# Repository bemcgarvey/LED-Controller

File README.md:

# LED Controller
 RC LED Controller

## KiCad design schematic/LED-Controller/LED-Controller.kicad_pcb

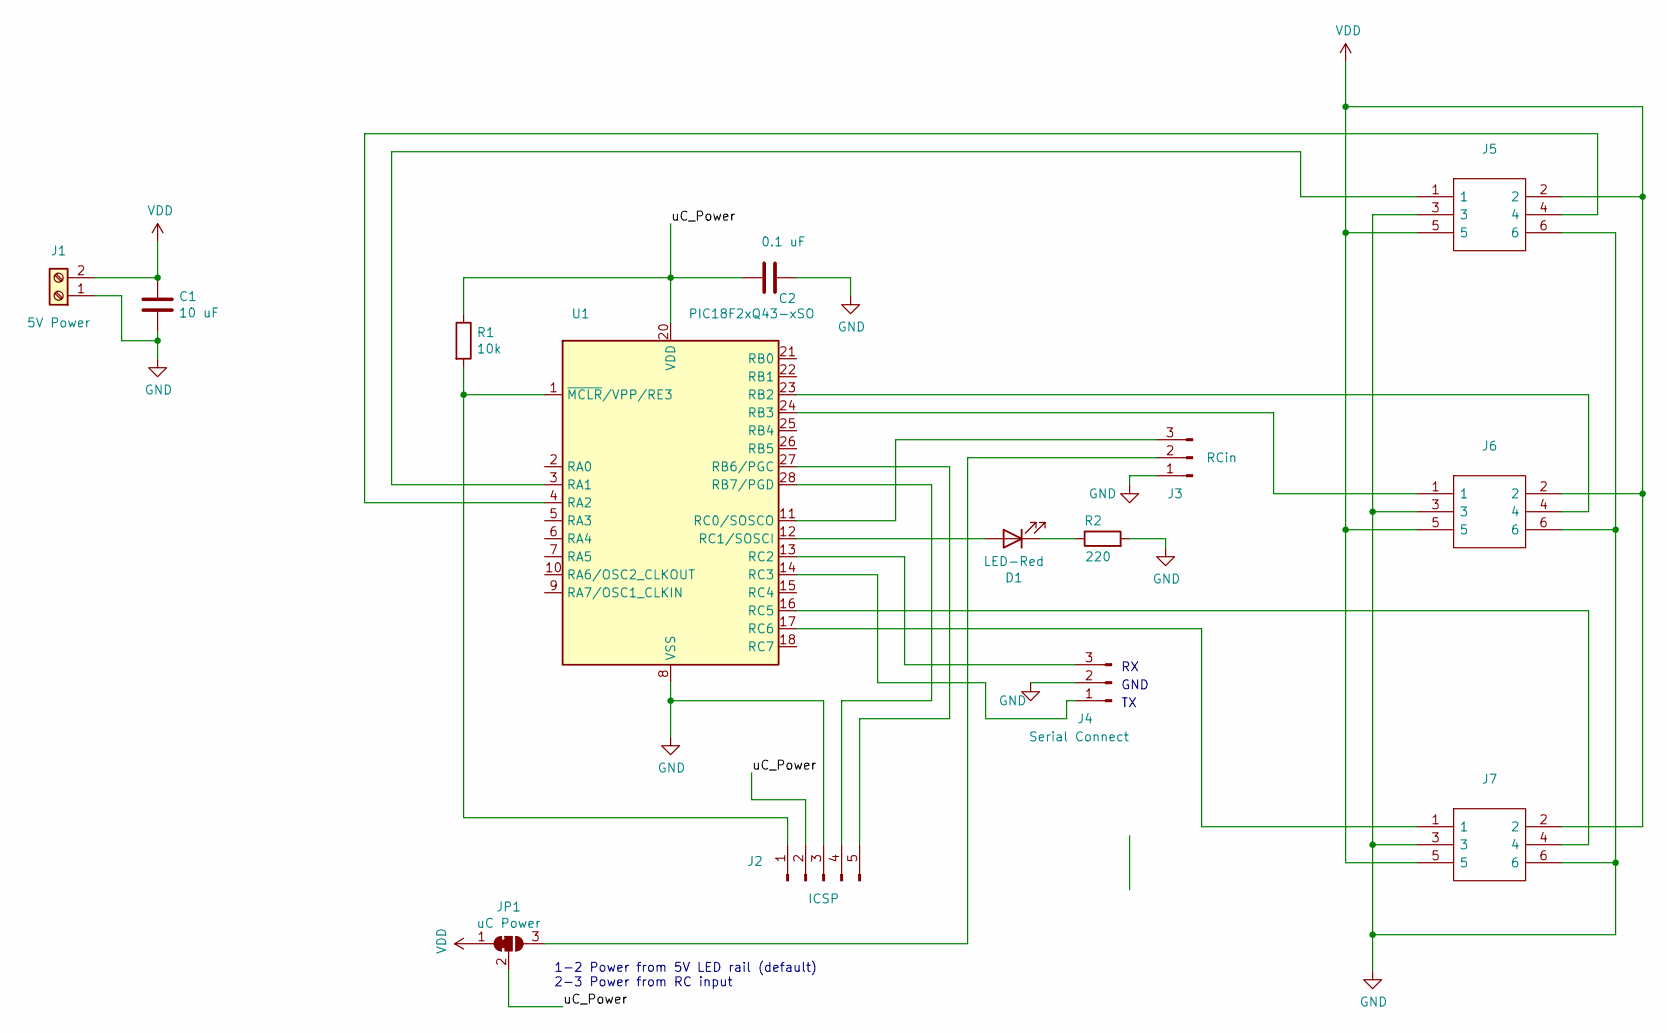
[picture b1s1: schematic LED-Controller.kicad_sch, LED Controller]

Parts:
C1: 10 uF; C_1206_3216Metric_Pad1.33x1.80mm_HandSolder
C2: 0.1 uF; C_0603_1608Metric_Pad1.08x0.95mm_HandSolder
D1: LED-Red; LED_0603_1608Metric_Pad1.05x0.95mm_HandSolder
J1: 5V Power; SolderWire-1sqmm_1x02_P5.4mm_D1.4mm_OD2.7mm
J2: ICSP; PinHeader_1x05_P2.54mm_Vertical
J3: RCin; PinHeader_1x03_P2.54mm_Horizontal
J4: Serial Connect; PinHeader_1x03_P2.54mm_Vertical
J5, J6, J7: TSW-102-08-L-T-RA; HDRRA6W64P254_3X2_508X254X810P; Mouser Part Number 200-TSW10208LTRA
JP1: uC Power; SolderJumper-3_P1.3mm_Bridged12_RoundedPad1.0x1.5mm_NumberL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
R1: 10k; R_0603_1608Metric
R2: 220; R_0603_1608Metric
U1: PIC18F2xQ43-xSO; SOIC-28W_7.5x17.9mm_P1.27mm

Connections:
/uC_Power: C2.2, J2.2, JP1.2 (C), R1.1, U1.20 (VDD)
GND: C1.2, C2.1, J1.1, J2.3, J3.1, J4.2, J5.3, J5.6, J6.3, J6.6, J7.3, J7.6, R2.2, U1.8 (VSS), U1.19 (VSS)
unnamed: D1.1 (K), R2.1
unnamed: D1.2 (A), U1.12 (RC1/SOSCI)
unnamed: J2.1, R1.2, U1.1 (~MCLR/VPP/RE3)
unnamed: J2.4, U1.28 (RB7/PGD)
unnamed: J2.5, U1.27 (RB6/PGC)
unnamed: J3.2, JP1.3 (B)
unnamed: J3.3, U1.11 (RC0/SOSCO)
unnamed: J4.1, U1.14 (RC3)
unnamed: J4.3, U1.13 (RC2)
unnamed: J5.1, U1.3 (RA1)
unnamed: J5.4, U1.4 (RA2)
unnamed: J6.1, U1.24 (RB3)
unnamed: J6.4, U1.23 (RB2)
unnamed: J7.1, U1.17 (RC6)
unnamed: J7.4, U1.16 (RC5)
VDD: C1.1, J1.2, J5.2, J5.5, J6.2, J6.5, J7.2, J7.5, JP1.1 (A)

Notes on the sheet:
GND
1-2 Power from 5V LED rail (default) 2-3 Power from RC input

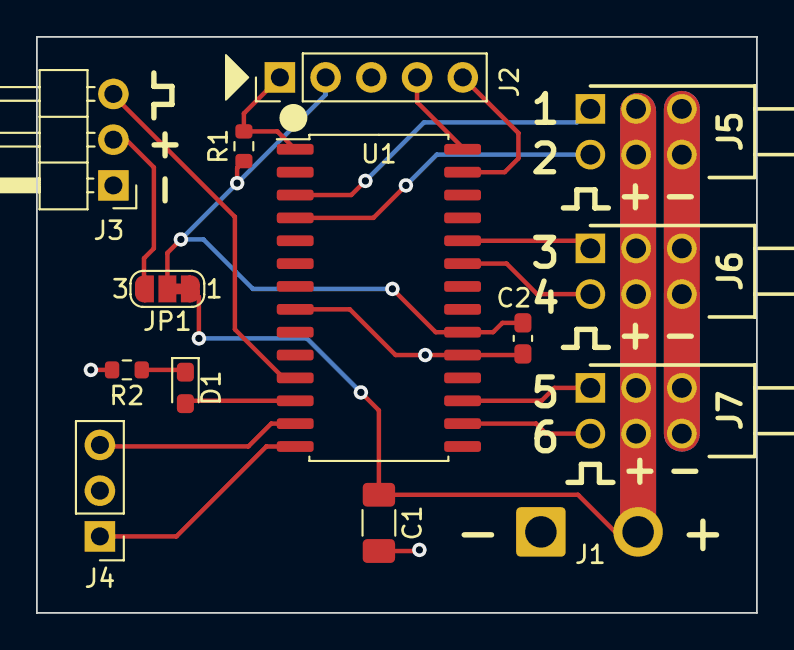
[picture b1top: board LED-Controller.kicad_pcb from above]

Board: 2 copper layers, 40.0 x 32.0 mm, 14 parts (0 on the bottom side), 18 nets.

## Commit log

2021-02-15 Added KiCad project
2021-02-15 Schematic first draft
2021-02-15 Initial pcb
    Some schematic adjustments to improve pcb layout
2021-02-16 Added flexible power for uController
2021-02-17 Changed connectors
2021-02-17 Complete pcb layout
2021-02-17 Completed pcb
2021-02-18 removed unused footprint
2021-02-18 Created firmware project
2021-02-18 Created client project
2021-03-05 Switched to PIC18F2xK42
2021-03-05 Labeled serial output on schematic
2021-03-06 Initial SPI and CLC code working
2021-03-06 Basic UART functionality tested
2021-03-06 RC input tested.
    All basic functionality confirmed. PCB seems correct
2021-03-07 All led outputs working
2021-03-08 Implemented 10Hz system timer
2021-03-08 Serial tested between client and firmware
2021-03-09 Basic layout
2021-03-10 Merged .gitignore files
2021-03-11 Rough LED display functionality
2021-03-12 Adjusted HDPI scaling
2021-03-13 Basic led editing working
2021-03-13 Saved colors in registry
2021-03-13 Improved saving of custom colors
2021-03-13 Fixes to dialog appearance
2021-03-13 All output displays connected. Scrolling added to main window
2021-03-14 Added version info and about dialog
2021-03-14 Renamed some classes and files
2021-03-14 Combined outputs into single class
    Fixed names for promoted widgets in ui 's
2021-03-15 Implemented save and open
2021-03-15 Added file header with id and version
2021-03-15 Changed file id
2021-03-15 Fixed onTIme display and save/load
2021-03-15 Added Test button stub to pattern edit dialog
    Still needs to transfer pattern to device
2021-03-16 Serial handshake working
2021-03-16 Reordered byte stream. Fixed data before variable and little endian
2021-03-16 Read from device to client sort of working
2021-03-17 Read from device is working
2021-03-17 Added priority attribute to interrupts
2021-03-17 Write to device working
2021-03-18 Added ROM validation
2021-03-18 Interface improvements and correct checksum
2021-03-19 Improved pattern scrolling
2021-03-19 Prompt on modified implemented
2021-03-19 Added const to class members where appropriate
2021-03-19 Drag and drop implemented
2021-03-20 Test pattern feature implemented
    Minor cosmetic fixes
    Renumbered outputs in firmware to start with zero
2021-03-20 Eliminated size calculation - now stored as variable
2021-03-20 Fixed scrolling bug and lack of update after read
2021-03-21 Minor changes
    Corrected modified value after read
    Prevented test when not connected
2021-03-21 LED display and pattern timing is working
2021-03-21 Moved some code out of the ISRs
2021-03-21 Added some clear() calls to serial code
2021-03-22 RC actions implemented
2021-03-22 Added RC monitor
2021-03-22 Added icon and button images
2021-03-23 Small cosmetic changes
2021-03-23 Minor fixes
2021-03-27 Compiles. Serial is working
2021-03-27 Cleaned up file headers
2021-03-27 Write to ROM and outputs working
2021-03-27 All outputs use CLC and cleaned up file headers
2021-03-27 Increased delay between clear and setLEDs
2021-03-27 Improved memory handling
    Configured for 18F26Q43 and 18F27Q43
2021-03-28 Added file name to window title
2021-03-28 Removed temp file from tracking
2021-03-28 Removed temp file
2021-03-28 Changed .gitignore to include project files
2021-03-28 Updated schematic to 18F2xQ43
2021-03-28 Fixed .gitignore to include project files
2021-03-29 Schematic text updated
2021-03-29 Minor fixes to firmware. Set version to 1.1
2021-03-30 Added reset colors to pattern dialog
2021-03-30 Added Fill and Gradient Fill
2021-03-30 Changed On Time spinbox to adaptive
2021-03-30 Improved spinbox behavior
2021-03-30 Improved drag and drop
    When dropping a longer pattern the destination is resized.
2021-03-30 Added rotate pattern option to client
2021-03-31 Added rotate pattern feature
2021-04-01 Added bounce action
    RC input is broken
2021-04-01 Set firmware to v1.0 Release version for firmware and client
2021-04-09 Added step feature to client
2021-04-09 Added step feature to firmware
2021-04-09 Renamed change log file
2021-04-18 Added command line file open
2021-08-23 Moved serial connected to edge of board
2021-11-05 Fixed a bug when dragging a pattern
2021-11-06 Update to Qt 6.2.
2022-01-19 Converted to KiCad 6
